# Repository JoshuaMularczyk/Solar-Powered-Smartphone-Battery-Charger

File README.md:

# Solar Smartphone Charger
This project applies skills of Power Electronics to create, deign, and construct a solar powered battery charger. My partner [Christian Williams](https://github.com/cwill713) and I were tasked by our professor [Dr. Rob Frohne](https://github.com/frohro) with coming up with a project for our Power Electronics class that incorporated what we were learning in the coursework. We decided to take what we were learning about step-down converters and design a charger for a smartphone in which the power source was a solar panel.

## Design Objectives:
- Output 5V from a higher input voltage
- Allow 1 amphere to be drawn into the smartphone
- Inexpensive to build ($20-$30 Budget)

## Overview

The power electronics project that [Christian Williams](https://github.com/cwill713) and I decided on was based around the specifications of new generation iPhone. We knew that Apple is picky with their products, so if we could get it to work with an iPhone it should, in theory, work with Android as well. I decided to use the [LM3478](https://www.ti.com/lit/ds/symlink/lm3478.pdf?HQS=dis-dk-null-digikeymode-dsf-pf-null-wwe&ts=1654180125781&ref_url=https%253A%252F%252Fwww.ti.com%252Fgeneral%252Fdocs%252Fsuppproductinfo.tsp%253FdistId%253D10%2526gotoUrl%253Dhttps%253A%252F%252Fwww.ti.com%252Flit%252Fgpn%252Flm3478) High-Efficiency Low-Side N-Channel Controller for our Switching Regulator. This is the heart of our circuit and allows for a reccomended 2.97-40V input volage and a peak driver output current of 1A. This chip can withstand a typical input current of 2.7A and a max of 3.3A. We used a 5W 12V Solar Panel to ensure that our smartphone would charge in average conditions.

## Rev 7 Design

This is the most updated KiCad schematic for my circuit design. I used the Texas Instrument [Webench Power Designer](https://www.ti.com/design-resources/design-tools-simulation/webench-power-designer.html) to generate this step-down circuit. I used the majority of the components specified by the power designer with the exception of some values. These can be found in the [BOM](https://github.com/JoshuaMularczyk/Solar-Smartphone-Charger/tree/main/BOMs) I specified a 5V minimum as well as a 12V maximum based on what would most likely be coming out of the solar panel. I also specified 1A for my maximum output current and 5V for my output voltage. The efficiency of this circuit was given at 84.1% by Webench.

### Voltage Dividers for USB

The voltages that needed to be applied to the Vbus, D+, and D- pin were found in the following websites: [Pinout for USB](http://static.righto.com/files/charger-schematic.pdf) and [Values based on different Ampheres](https://kb.plugable.com/usb-hubs-cables-switches/usb-device-charging). *Note since we are using 1A ouput the Vbus pin needs 5V, the D- pin needs 2V, and the D+ pin needs 2.7V*
## Rev 7 Simulation
I simulated our circuit in LTSpice

LTSpice has most of the components needed, but I had to import a library for the LM3478. I found this library in a [project log](https://hackaday.io/project/27899-nixie-tube-power-supply/log/69767-ltspice) by [Paul Andrews](https://github.com/judge2005) on Hackaday. That library was causeing some errors in LTSpice so I did some research and realized I needed to add two more "0" place holders after each "PULSE" statement. The updated library that I used LM3478 can be downloaded [here](https://github.com/JoshuaMularczyk/Solar-Smartphone-Charger/blob/main/Simulations/LM3478_TRANS.lib). The second library I needed was for the csd17553q5a mosfet. I found this library on the [Texas Instrument](https://www.ti.com/product/CSD17553Q5A#design-tools-simulation) page. This library can be downloaded [here](https://github.com/JoshuaMularczyk/Solar-Smartphone-Charger/blob/main/Simulations/CSD17553Q5A.lib). The schottkey diode used in the simulation is also not the exact same component as used in the schematic but another schottkey diode with the same specifications was used in its place. The simulation ran over night to get to 7 ms. The prolonged period of time was likely due to the laptop it was running on as well as the coupled inductors in the circuit.

### Voltage Outputs (5V 2.7V 2V)

This simulation shows the voltages going into each of our three USB output pins (5V, 2.7V, 2V).

### Input and Output Current

This simulation shows the two different currents in our circuit. The green trace represents the current going into the LM3478. It starts at about 270mA and trails off close to 0A. The blue trace represents the current being pulled from the 5-ohm load resistor which is taking the place of an iPhone. The iPhone needs to draw around 1A of current and as seen in the simulation it will achieve this.

## Rev 7 PCB Design

We had our boards sourced from [JLCPCB](https://jlcpcb.com/VGS?utm_source=gg_vgs&utm_medium=cpc&gclid=Cj0KCQjwqPGUBhDwARIsANNwjV4Y9aU908uwwHsgXCAJ3L9PZ44l-hPgCvsU4kgto-ll1H0iRJroh1UaAsKwEALw_wcB), who have an offer going of 5, 2-layer, 100x100mm boards for $2. I then designed the board to fit these specifications and send it in for printing.

## Rev 6 Testing

My partner and I decided to construct a [Build and Test Plan](https://github.com/JoshuaMularczyk/Solar-Smartphone-Charger/blob/main/Milestone%20Reports/Build%20and%20Test%20Plan.xlsx) while we waited for our parts to come in from JLCPCB and Digikey. It helped us think through ways of testing things in stages without causing the destructions of parts.

My partner and I each constructed a separate board and tested to see if it worked. After constructing the boards we used a 0-18V 1A power supply and realized that the boards were not allowing our iPhones to charge. We plugged in a nearby TI-84 Plus CE calculator that was rated to charge at 5V 0.5A and it started charging. We then decided to switch to a bigger power supply rated for 24V 3A and plugged in an Android which began to charge. The iPhone still would not charge. After some research about Apple devices, a fellow colleague, [Caydn Maddocks](https://github.com/Maddca) and I discovered that Apple was extra particular and required voltages to the D+ and D- pins of the USB connector. The specific voltages differ based on the current being drawn (we used 2.7V to D+ and 2V to D-). This can be seen in the "Voltage Dividers for USB" section above. The process of fixing this can be seen in the issues section [here](https://github.com/JoshuaMularczyk/Solar-Smartphone-Charger/issues?q=is%3Aissue+is%3Aclosed).

Next, we connected our 5W 12V solar panels to the converter and took them outside to get direct sunlight. Once the solar panel was propped up to be perpendicular to the sun, I plugged in my iPhone and it started charging. It takes quite a bit of time to charge with 5W so I recommend getting a higher wattage solar panel for faster charging.

## Rev 6 Results

The image on the left shows the voltage being supplied to the iPhone and the image on the right shows the current being drawn by the iPhone.

Here we can see that using the power supply, our circuits is around 93.7% efficient ((4.88V*0.96A)/(5W)). We also tested this circuit with voltages from 5-12V from the power supply and the output stayed at a constant 4.8-4.9V.

The Solar Smartphone Charger worked as expected and was able to charge smartphones, Apple and Android, during a sunny day. You can see more photos of the finished product on the [wiki](https://github.com/JoshuaMularczyk/Solar-Smartphone-Charger/wiki/Photos) here!

We measured a 4.74V 0.98A output from our circuit using a solar panel. This gives us an efficiency of 92.9% given that our solar panel was actually outputting 5W.

Click [here](https://youtu.be/SS7m2UqrDPg) to watch a video demonstration of the finished project!

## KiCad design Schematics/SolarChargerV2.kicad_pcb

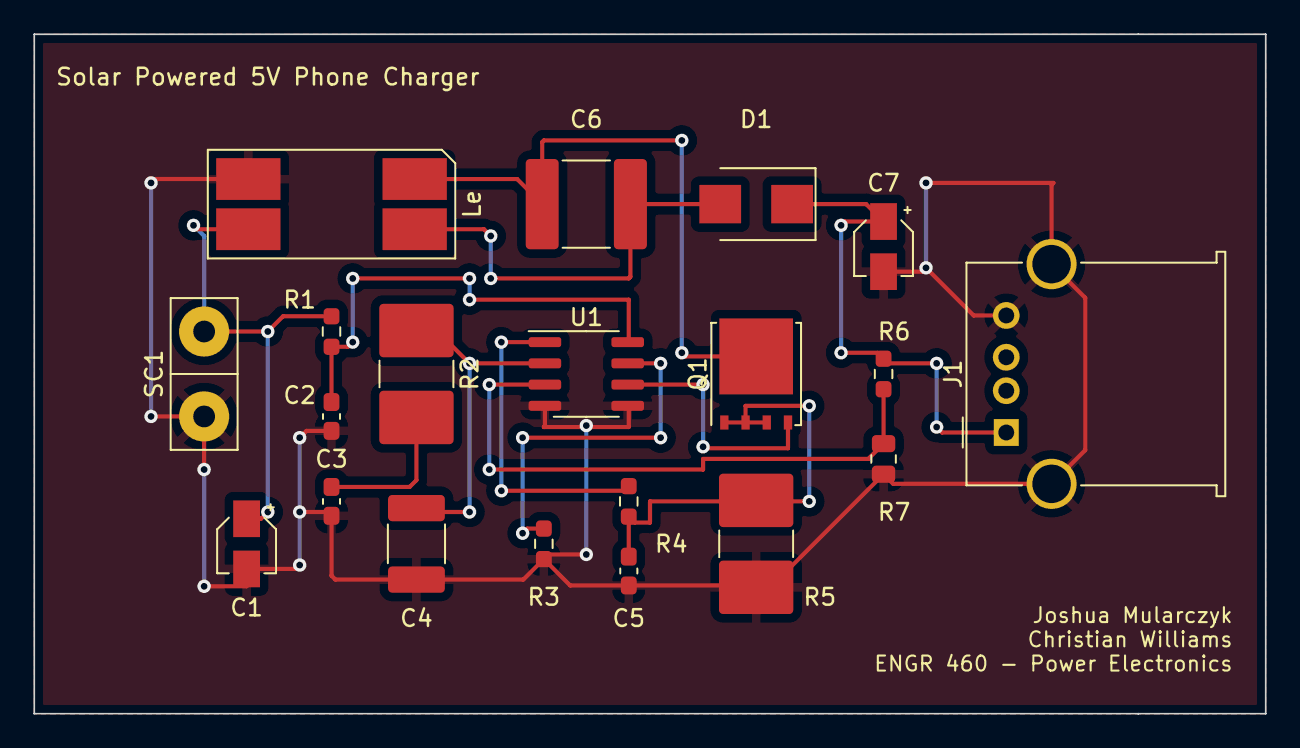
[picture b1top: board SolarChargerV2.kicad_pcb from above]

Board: 2 copper layers, 73.7 x 40.6 mm, 20 parts (0 on the bottom side), 13 nets.

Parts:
C1: 10u; CP_Elec_3x5.3
C2: 100n; C_0603_1608Metric_Pad1.08x0.95mm_HandSolder
C3: 82n; C_0603_1608Metric_Pad1.08x0.95mm_HandSolder
C4: 195p; C_1812_4532Metric_Pad1.57x3.40mm_HandSolder
C5: 1n; C_0603_1608Metric_Pad1.08x0.95mm_HandSolder
C6: 1u; C_2220_5650Metric_Pad1.97x5.40mm_HandSolder
C7: 77u; CP_Elec_3x5.3
D1: B230; D_SMB
J1: USB_A; USB_A_Molex_67643_Horizontal
Le: 10u; DRQ
Q1: CSD17553Q5A; TDSON-8-1
R1: 20; R_0603_1608Metric_Pad0.98x0.95mm_HandSolder
R2: 909; R_2816_7142Metric_Pad3.20x4.45mm_HandSolder
R3: 51.1k; R_0603_1608Metric_Pad0.98x0.95mm_HandSolder
R4: 100; R_0603_1608Metric_Pad0.98x0.95mm_HandSolder
R5: 25m; R_2816_7142Metric_Pad3.20x4.45mm_HandSolder
R6: 29.4k; R_0603_1608Metric_Pad0.98x0.95mm_HandSolder
R7: 10k; R_0805_2012Metric
SC1: Solar_Cell; SIP-2
U1: LM3478MA_NOPB; SOIC-8_3.9x4.9mm_P1.27mm

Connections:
GND: C1.2, C2.2, C3.2, C4.2, C5.2, C7.2, J1.4 (GND), J1.5 (Shield), Le.4, R3.2, R5.2, R7.2, SC1.2 (-), U1.4 (AGND), U1.5 (PGND)
unnamed: C1.1, Le.3, R1.1, SC1.1 (+)
unnamed: C2.1, R1.2, U1.8 (VIN)
unnamed: C3.1, R2.2
unnamed: C4.1, R2.1, U1.2 (COMP)
unnamed: C5.1, Q1.1 (S), Q1.2 (S), Q1.3 (S), R4.2, R5.1
unnamed: C6.1, Le.1, Q1.5 (D)
unnamed: C6.2, D1.2 (A), Le.2
unnamed: C7.1, D1.1 (K), J1.1 (VBUS), R6.1
unnamed: Q1.4 (G), U1.6 (DR)
unnamed: R3.1, U1.7 (FA/SD)
unnamed: R4.1, U1.1 (ISEN)
unnamed: R6.2, R7.1, U1.3 (FB)

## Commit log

2022-04-19 Upload of first parts list
2022-04-19 Upload of file for milestones
2022-04-19 Upload of the second version of the solar charger schematic
2022-04-19 upload of schematic
2022-04-19 Upload of our LM3478 chip library for LTSpice
2022-04-19 Upload of the LTSpice simulation
2022-04-19 BOM file
2022-04-19 upload of a screen shot of the schematic
2022-04-25 updates and changes
2022-04-26 Final schematic and PCB created plus BOM and gerber files
2022-04-27 creation of drill files and two zip folders
2022-04-27 File rearangement and V3 of the project
2022-04-27 Version 4 created to swtich out mosfet, diode, and resistor
2022-04-28 Versions 4 created
2022-04-28 new files
2022-04-28 Final changes and Version 5
2022-04-28 Version 6 created
2022-05-01 final edits
2022-05-02 Milstone 4
2022-05-02 Clean up of files
2022-05-02 New HTML bom
2022-05-24 Version 7 created to add voltage divider (Iphone compatablility)
2022-06-03 Version 7 final changes
2022-06-06 quick fix of resistor values for voltage divider
2022-06-22 Create LICENSE
    created license for power electronics project
